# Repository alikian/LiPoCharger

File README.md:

# LiPo Battery Charger and Gauge

The purpose of this have a simple board to charge and monitor LiPo battery.

- LMR10510 Step-Down Voltage Regulator
- MCP73831 LiPo Battery charger and Guage

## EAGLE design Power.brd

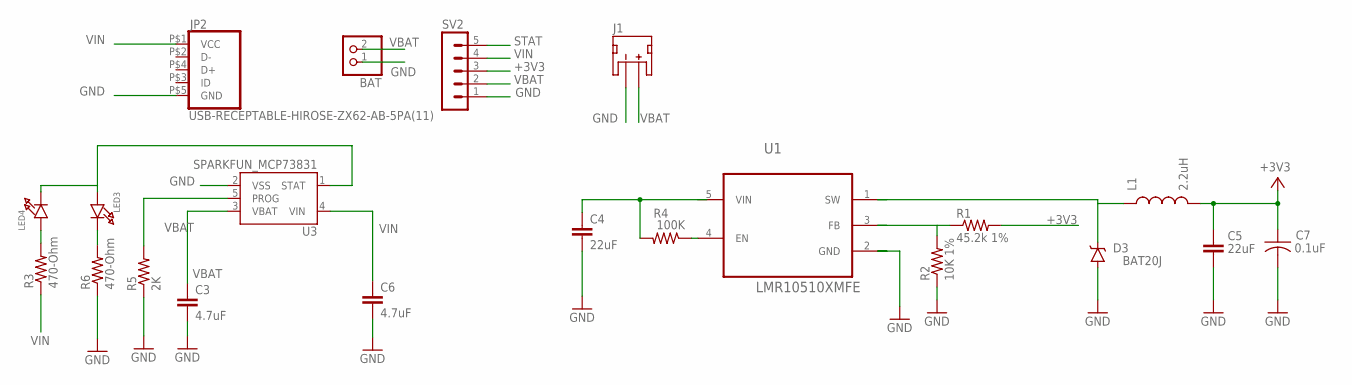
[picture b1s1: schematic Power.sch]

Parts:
BAT: PINHD-1X2; 1X02
C3, C6: 4.7uF; 0603-CAP
C4, C5: 22uF; C0603
C7: 0.1uF; C0402
D3: BAT20J; SOD-323
J1: JST_2MM_MALE; JST-2-SMD
JP2: USB-RECEPTABLE-HIROSE-ZX62-AB-5PA(11); HIROSE-ZX62-AB-5PA(11)
L1: 2.2uH; 0805
LED3, LED4: LED0603; CHIPLED_0603
R1: 45.2k 1%; 0603-RES
R2: 10K 1%; 0603-RES
R3, R6: 470-Ohm; 0603-RES
R4: 100K; R0402
R5: 2K; 0603-RES
SV2: MA05-1
U1: LMR10510XMFE; SOT95P270X145-5N
U3: SPARKFUN_MCP73831; SPARKFUN_SOT23-5

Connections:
+3V3: C5.1, C7.1, L1.2, R1.2, SV2.3
FB: R1.1, R2.2, U1.3 (FB)
GND: BAT.1, C3.2, C4.2, C5.2, C6.2, C7.2, D3.A, J1.1 (-), JP2.P$5 (GND), R2.1, R5.1, R6.1, SV2.1, U1.2 (GND), U3.2 (VSS)
unnamed: LED4.A, R3.2
unnamed: R4.1, U1.4 (EN)
unnamed: LED3.C, R6.2
PROG: R5.2, U3.5 (PROG)
STAT: LED3.A, LED4.C, SV2.5, U3.1 (STAT)
SW: D3.C, L1.1, U1.1 (SW)
VBAT: BAT.2, C3.1, C4.1, J1.2 (+), R4.2, SV2.2, U1.5 (VIN), U3.3 (VBAT)
VIN: C6.1, JP2.P$1 (VCC), R3.1, SV2.4, U3.4 (VIN)

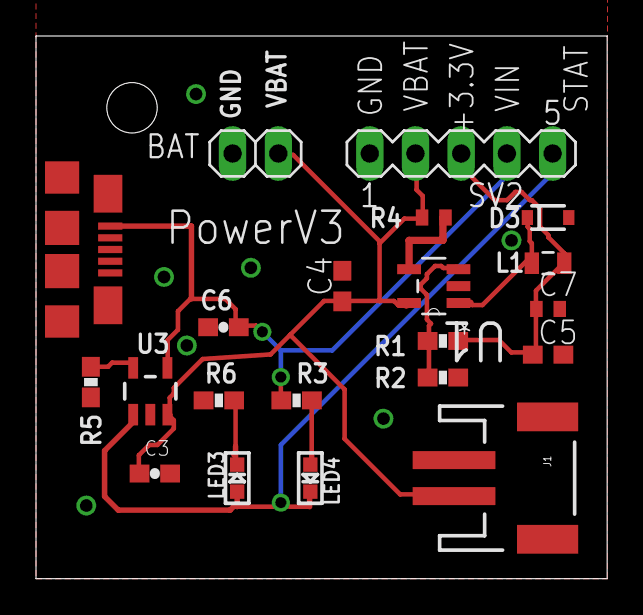
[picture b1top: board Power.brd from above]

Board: 2 copper layers, 31.7 x 30.1 mm, 21 parts (1 on the bottom side), 11 nets.

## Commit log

2015-02-26 :boom::camel: Added .gitattributes & .gitignore files
2015-02-26 Revert ":boom::camel: Added .gitattributes & .gitignore files"
    This reverts commit 82139e84f693e232b253fe26a74e3e071f79adfe.
2015-02-26 Added more comment
2015-02-26 Some clean up

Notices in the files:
parts and their libraries:
SparkFun-DiscreteSemi: Licensing: Creative Commons ShareAlike 4.0 International - https://creativecommons.org/licenses/by-sa/4.0
microbuilder: This work is placed in the public domain, and may be freely used for commercial and non-commercial work with the following conditions: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
